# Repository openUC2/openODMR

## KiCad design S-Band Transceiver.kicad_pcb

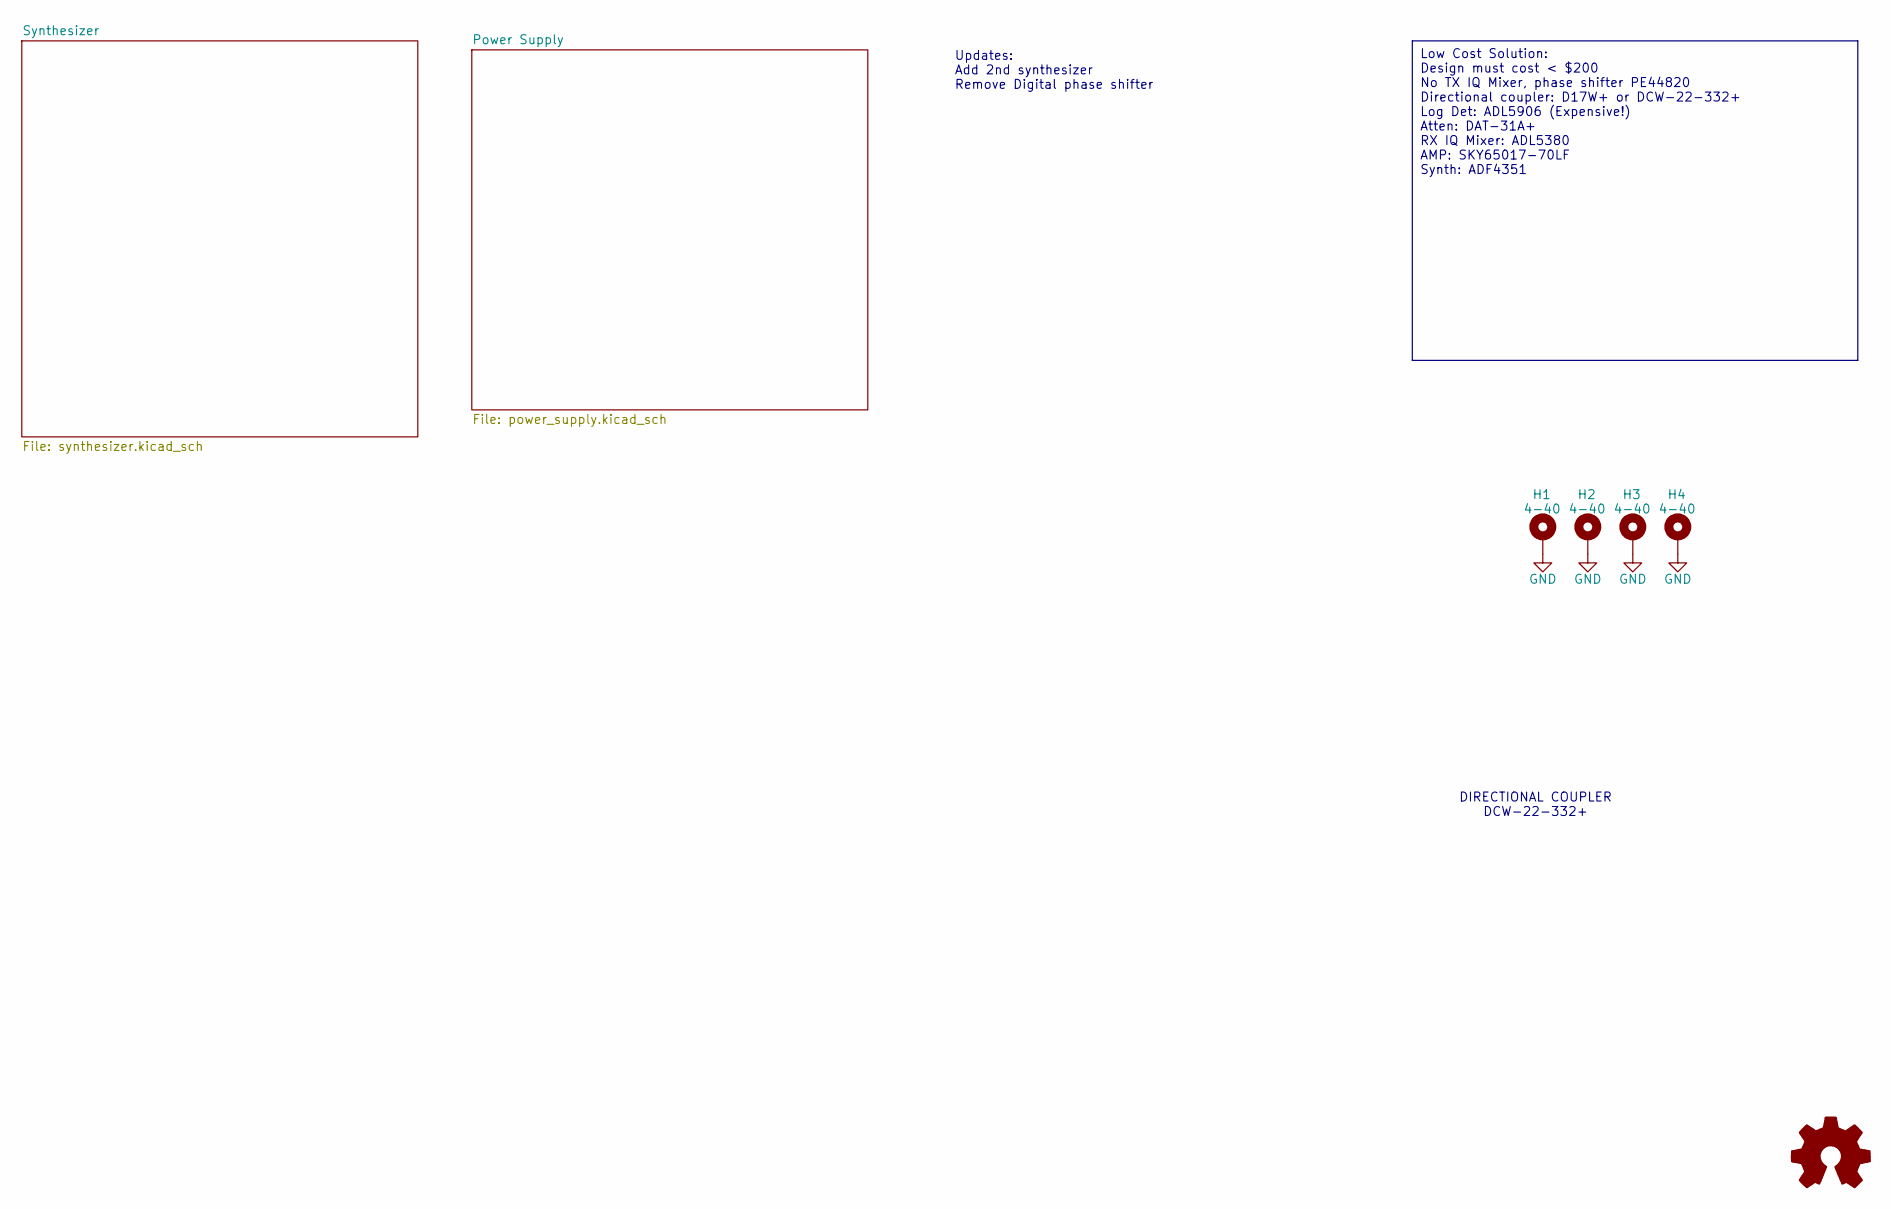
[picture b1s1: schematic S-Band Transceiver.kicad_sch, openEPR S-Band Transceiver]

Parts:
H1, H2, H3, H4: 4-40; 4-40_Hole_Pad

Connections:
GND: H1.1, H2.1, H3.1, H4.1; also elsewhere on the board

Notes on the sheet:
Low Cost Solution: Design must cost < $200 No TX IQ Mixer, phase shifter PE44820 Directional coupler: D17W+ or DCW-22-332+ Log Det: ADL5906 (Expensive!) Atten: DAT-31A+ RX IQ Mixer: ADL5380 AMP: SKY65017-70LF Synth: ADF4351
Updates: Add 2nd synthesizer Remove Digital phase shifter
DIRECTIONAL COUPLER DCW-22-332+

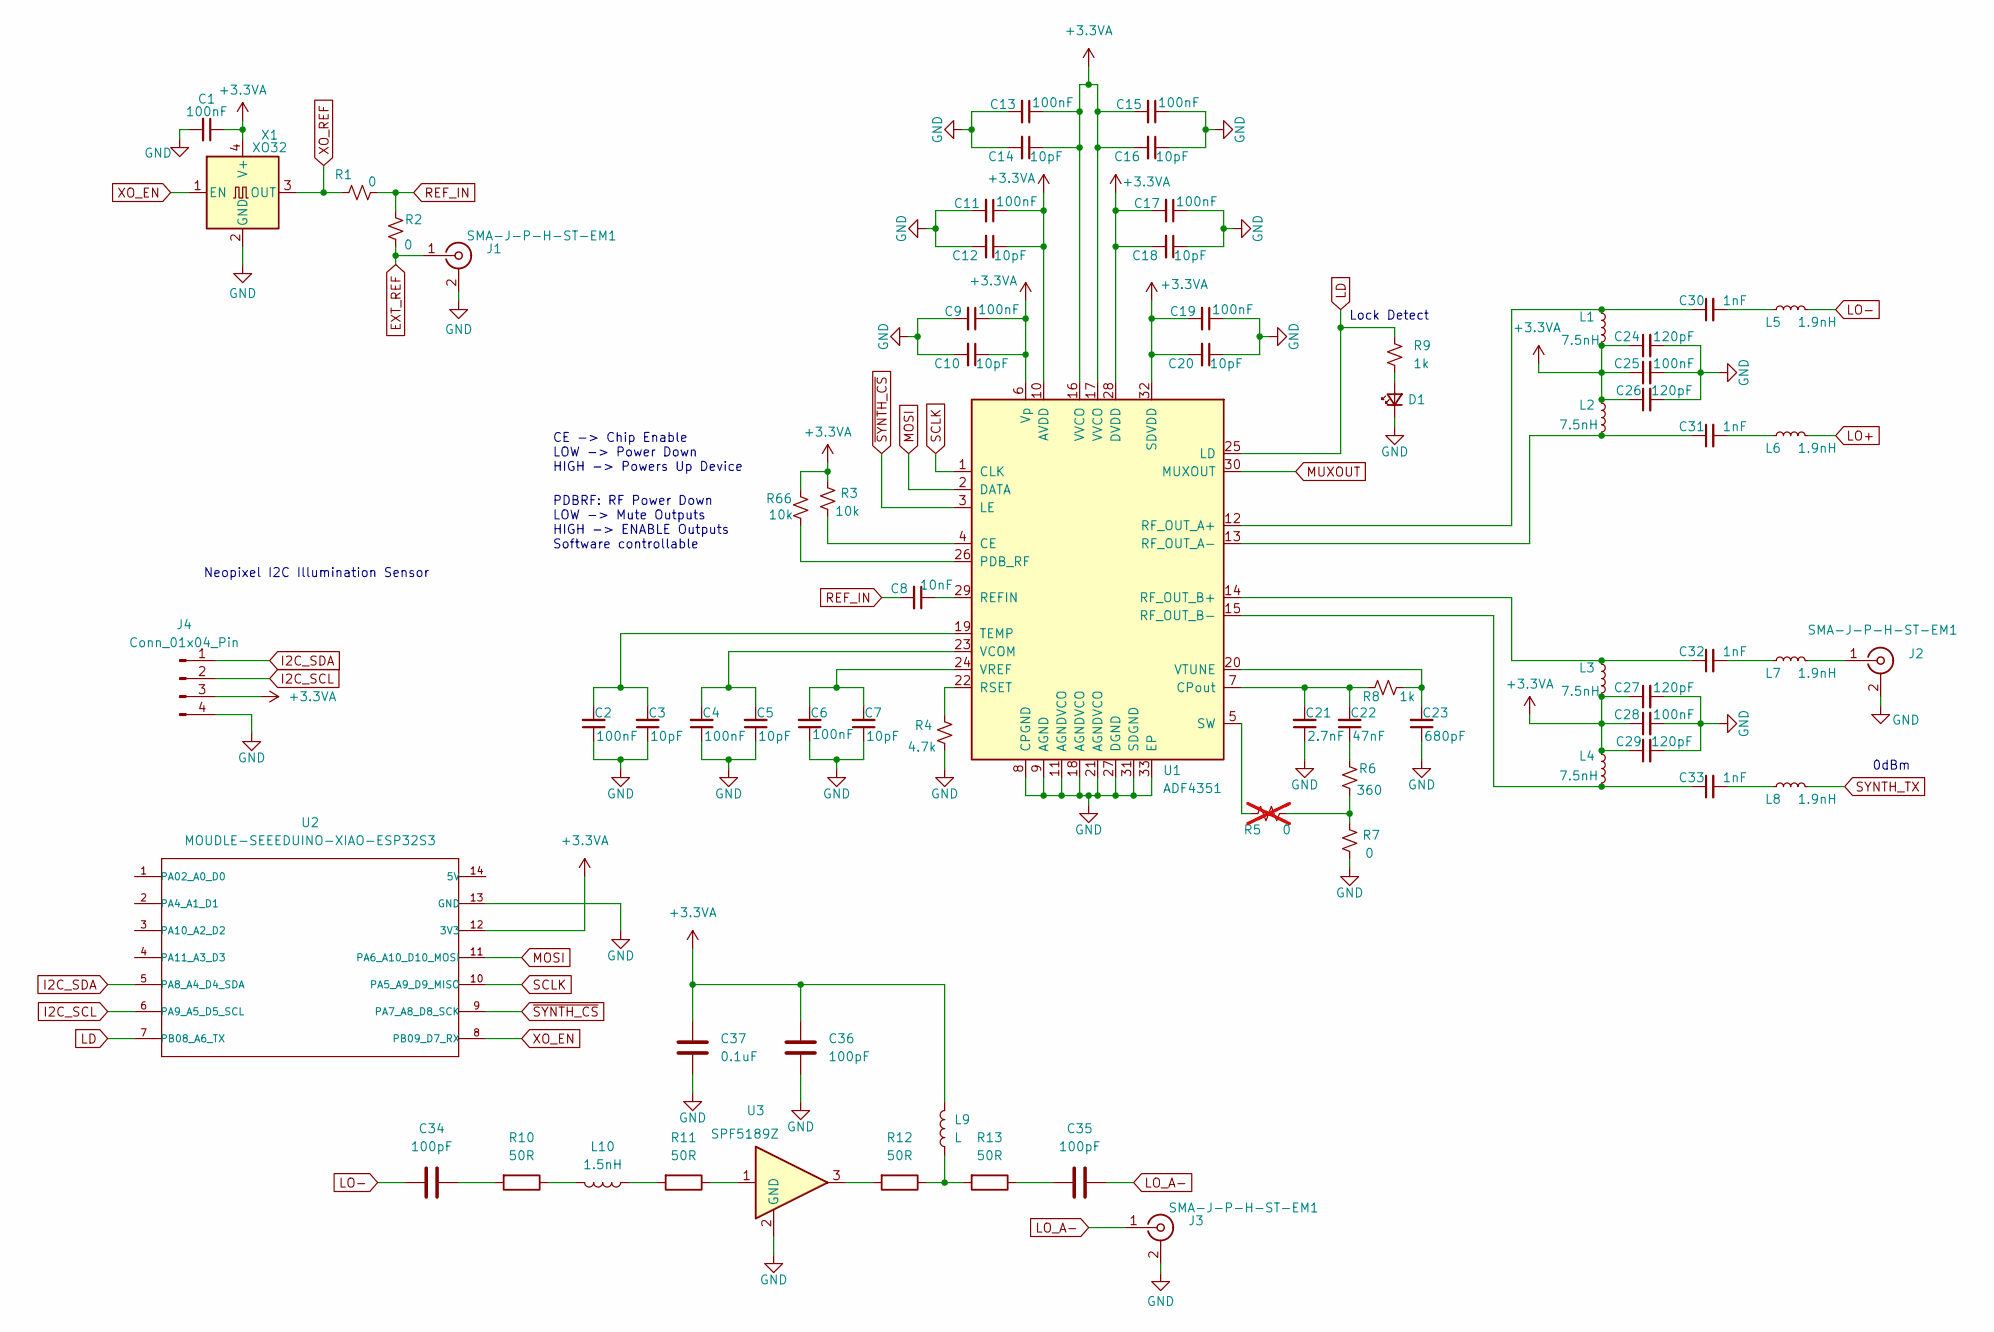
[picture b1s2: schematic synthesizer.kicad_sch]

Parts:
C1, C2, C4, C6, C9, C11, C13, C15, C17, C19, C25, C28: 100nF; C_0402_1005Metric
C3, C5, C7, C10, C12, C14, C16, C18, C20: 10pF; C_0402_1005Metric
C8: 10nF; C_0402_1005Metric
C21: 2.7nF; C_0603_1608Metric
C22: 47nF; C_0603_1608Metric
C23: 680pF; C_0603_1608Metric
C24, C26, C27, C29: 120pF; C_0402_1005Metric
C30, C31, C32, C33: 1nF; C_0402_1005Metric
C34, C35, C36: 100pF; C_0603_1608Metric
C37: 0.1uF; C_0603_1608Metric
D1: 150080VS75000; LED_0805_2012Metric
J1, J2, J3: SMA-J-P-H-ST-EM1; SMA_Samtec_SMA-J-P-X-ST-EM1_EdgeMount; Digikey SAM8857-ND
J4: Conn_01x04_Pin; JST_EH_B4B-EH-A_1x04_P2.50mm_Vertical
L1, L2, L3, L4: 7.5nH; L_0402_1005Metric
L5, L6, L7, L8: 1.9nH; L_0402_1005Metric
L9: L
L10: 1.5nH; L_0402_1005Metric
R1, R2, R7: 0; R_0603_1608Metric
R3, R66: 10k; R_0603_1608Metric
R4: 4.7k; R_0603_1608Metric
R5: 0; R_0603_1608Metric; not fitted
R6: 360; R_0603_1608Metric
R8, R9: 1k; R_0603_1608Metric
R10, R11, R12, R13: 50R; R_0603_1608Metric
U1: ADF4351; LFCSP-32-1EP_5x5mm_P0.5mm_EP3.25x3.25mm; Digikey 505-ADF4351BCPZ-RL7CT-ND
U2: MOUDLE-SEEEDUINO-XIAO-ESP32S3; MOUDLE14P-SMD-2.54-21X17.8MM
U3: SPF5189Z; SOT-89-3
X1: XO32; Oscillator_SMD_EuroQuartz_XO32-4Pin_3.2x2.5mm

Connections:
+3.3VA: C1.1, C9.1, C10.1, C11.1, C12.1, C13.1, C14.1, C15.2, C16.2, C17.2, C18.2, C19.2, C20.2, C24.1, C25.1, C26.1, C27.1, C28.1, C29.1, C36.1, C37.1, J4.3, L1.2, L2.1, L3.2, L4.1, L9.2, R3.2, R66.1, U1.6 (Vp), U1.10 (AVDD), U1.16 (VVCO), U1.17 (VVCO), U1.28 (DVDD), U1.32 (SDVDD), U2.12 (3V3), X1.4 (V+); also elsewhere on the board
EXT_REF: J1.1 (In), R2.1
GND: C1.2, C2.1, C3.1, C4.1, C5.1, C6.1, C7.1, C9.2, C10.2, C11.2, C12.2, C13.2, C14.2, C15.1, C16.1, C17.1, C18.1, C19.1, C20.1, C21.1, C23.1, C24.2, C25.2, C26.2, C27.2, C28.2, C29.2, C36.2, C37.2, D1.1 (K), J1.2 (Ext), J2.2 (Ext), J3.2 (Ext), J4.4, R4.2, R7.1, U1.8 (CPGND), U1.9 (AGND), U1.11 (AGNDVCO), U1.18 (AGNDVCO), U1.21 (AGNDVCO), U1.27 (DGND), U1.31 (SDGND), U1.33 (EP), U2.13 (GND), U3.2 (GND), X1.2 (GND); also elsewhere on the board
I2C_SCL: J4.2, U2.6 (PA9_A5_D5_SCL)
I2C_SDA: J4.1, U2.5 (PA8_A4_D4_SDA)
LD: R9.1, U1.25 (LD), U2.7 (PB08_A6_TX)
LO+: L6.2
LO-: C34.2, L5.2
LO_A-: C35.1, J3.1 (In)
MOSI: U1.2 (DATA), U2.11 (PA6_A10_D10_MOSI)
MUXOUT: U1.30 (MUXOUT)
unnamed: C22.1, R6.2
unnamed: C30.2, L5.1
unnamed: C31.2, L6.1
unnamed: C32.2, L7.1
unnamed: C33.2, L8.1
unnamed: C34.1, R10.2
unnamed: C35.2, R13.1
unnamed: D1.2 (A), R9.2
unnamed: J2.1 (In), L7.2
unnamed: L9.1, R12.1, R13.2
unnamed: L10.1, R11.2
unnamed: L10.2, R10.1
unnamed: R5.1, R6.1, R7.2
unnamed: R11.1, U3.1
unnamed: R12.2, U3.3
unnamed: R3.1, U1.4 (CE)
unnamed: C21.2, C22.2, R8.1, U1.7 (CPout)
unnamed: R66.2, U1.26 (PDB_RF)
unnamed: C8.1, U1.29 (REFIN)
unnamed: C30.1, L1.1, U1.12 (RF_OUT_A+)
unnamed: C31.1, L2.2, U1.13 (RF_OUT_A-)
unnamed: C32.1, L3.1, U1.14 (RF_OUT_B+)
unnamed: C33.1, L4.2, U1.15 (RF_OUT_B-)
unnamed: R4.1, U1.22 (RSET)
unnamed: R5.2, U1.5 (SW)
unnamed: C2.2, C3.2, U1.19 (TEMP)
unnamed: C4.2, C5.2, U1.23 (VCOM)
unnamed: C6.2, C7.2, U1.24 (VREF)
unnamed: C23.2, R8.2, U1.20 (VTUNE)
REF_IN: C8.2, R1.2, R2.2
SCLK: U1.1 (CLK), U2.10 (PA5_A9_D9_MISO)
SYNTH_TX: L8.2
XO_EN: U2.8 (PB09_D7_RX), X1.1 (EN)
XO_REF: R1.1, X1.3 (OUT)
~SYNTH_CS: U1.3 (LE), U2.9 (PA7_A8_D8_SCK)

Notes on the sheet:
Lock Detect
0dBm
PDBRF: RF Power Down LOW -> Mute Outputs HIGH -> ENABLE Outputs Software controllable
CE -> Chip Enable LOW -> Power Down HIGH -> Powers Up Device
Neopixel I2C Illumination Sensor

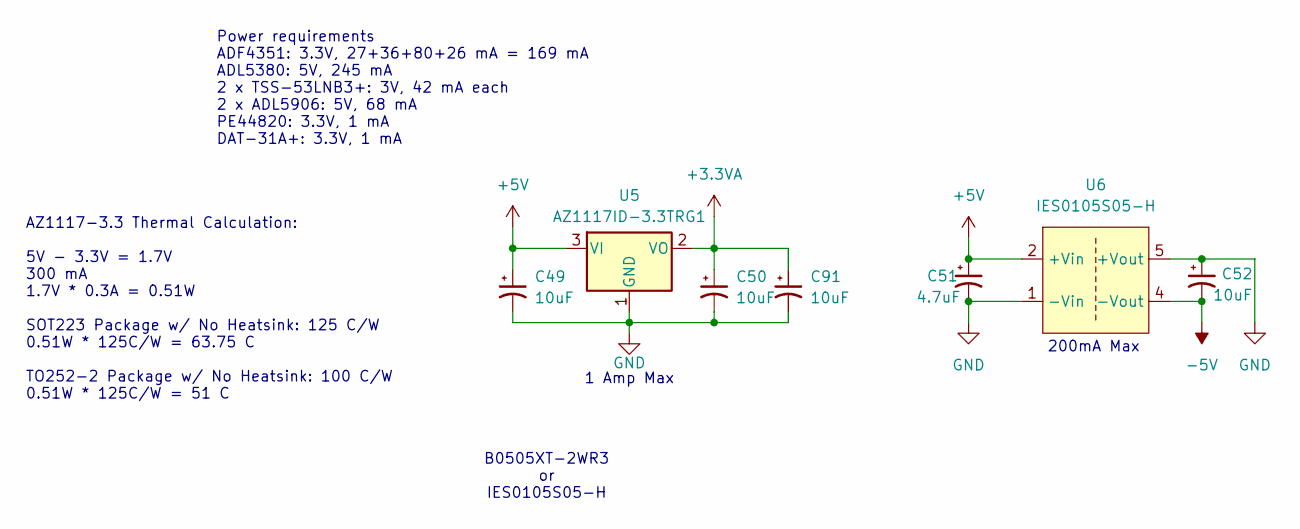
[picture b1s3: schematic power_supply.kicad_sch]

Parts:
C49, C50, C52, C91: 10uF; CP_EIA-3216-18_Kemet-A
C51: 4.7uF; CP_EIA-3216-18_Kemet-A
U5: AZ1117ID-3.3TRG1; TO-252-2; Digikey AZ1117ID-3.3TRG1-ND
U6: IES0105S05-H; Digikey 1470-IES0105S05-H-ND

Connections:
+3.3VA: C50.1, C91.1, U5.2 (VO); also elsewhere on the board
+5V: C49.1, C51.1, U5.3 (VI), U6.2 (+Vin)
-5V: C52.2, U6.4 (-Vout)
GND: C49.2, C50.2, C51.2, C52.1, C91.2, U5.1 (GND), U6.1 (-Vin), U6.5 (+Vout); also elsewhere on the board

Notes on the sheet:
B0505XT-2WR3 or IES0105S05-H
AZ1117-3.3 Thermal Calculation: 5V - 3.3V = 1.7V 300 mA 1.7V * 0.3A = 0.51W SOT223 Package w/ No Heatsink: 125 C/W 0.51W * 125C/W = 63.75 C TO252-2 Package w/ No Heatsink: 100 C/W 0.51W * 125C/W = 51 C
200mA Max
Power requirements ADF4351: 3.3V, 27+36+80+26 mA = 169 mA ADL5380: 5V, 245 mA 2 x TSS-53LNB3+: 3V, 42 mA each 2 x ADL5906: 5V, 68 mA PE44820: 3.3V, 1 mA DAT-31A+: 3.3V, 1 mA
1 Amp Max

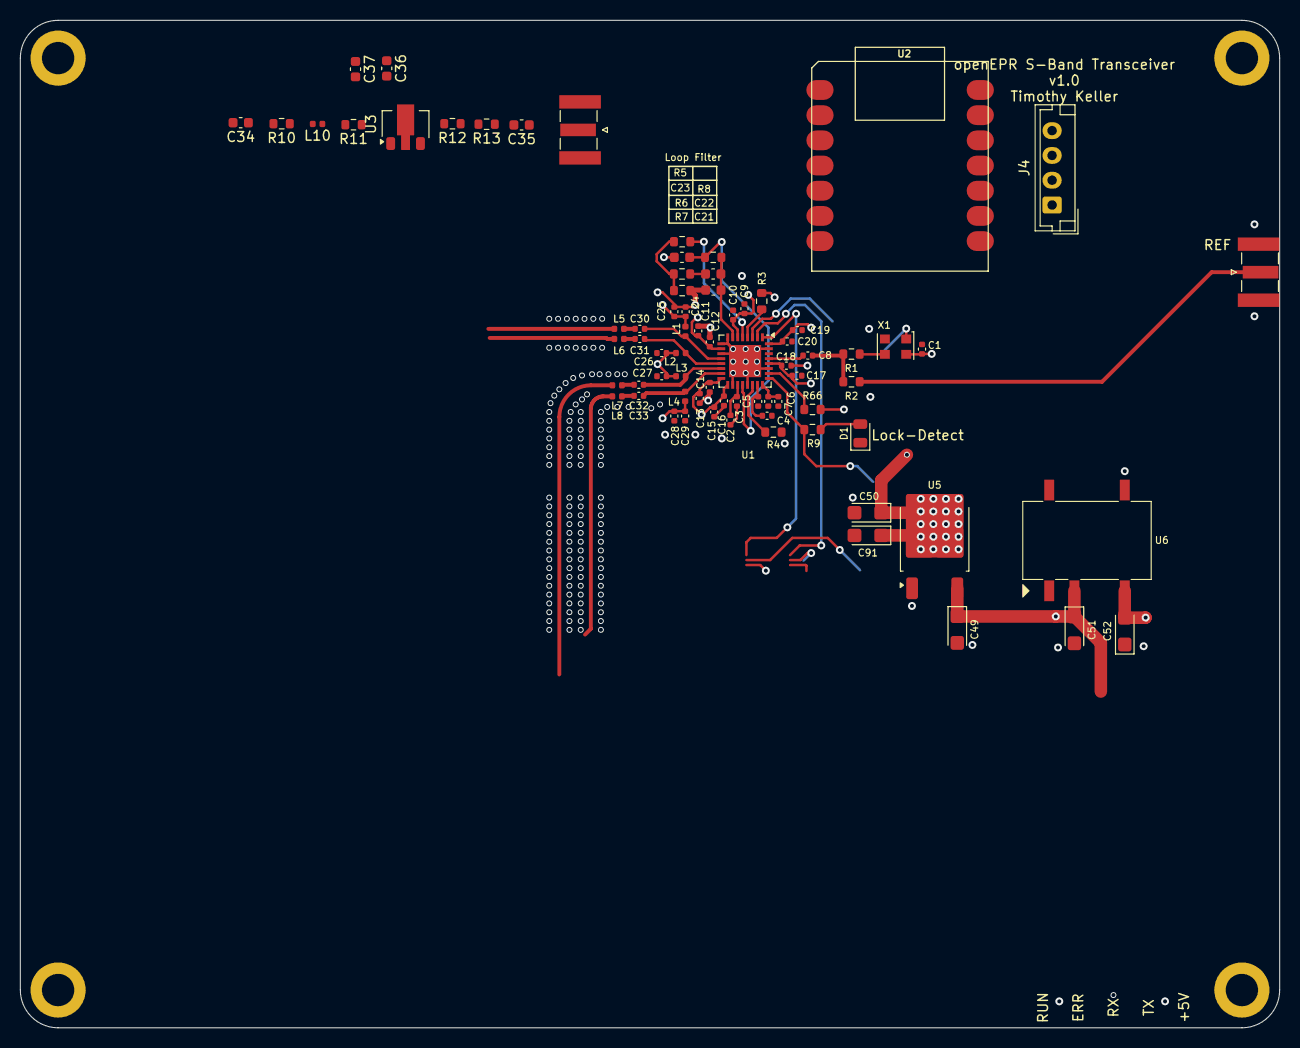
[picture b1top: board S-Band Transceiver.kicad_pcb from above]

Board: 4 copper layers, 127.0 x 101.6 mm, 79 parts (0 on the bottom side), 44 nets.

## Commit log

2025-01-16 initial change
2025-01-16 cleanup and renaming
2025-01-20 adding lastest state
